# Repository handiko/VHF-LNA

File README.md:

# MMIC VHF Low Noise Amplifier
VHF Low Noise Amplifier Circuit &amp; PCB using common MMIC. This unit is capable up to 1kW at 2m-band (144 MHz) and powered by +12V supply thru a separate cable (hi-power bias tee is not implemented). MMIC input is protected by a BPF. Therefore, due to the BPF insertion loss, the input NF is not extremely good, (only 1 dB NF approx.). All the Eagle and Gerber files are included.

## Schematic

## PCB (photos)
* Unpopulated

* Populated. The input port is at near the lower right relay and the output port is at near the lower left relay.

## BPF Response
BPF simulation file (using RFSim99) is included also.
Predicted performance:
* **S21 -3dB from 135.67MHz - 150.07MHz**
* **S21 -10dB from 131.1MHz - 154.5MHz**
* **S21 -0.02dB and S11 -23.86dB at 139.1MHz** (WXSat band)
* **S21 -0.31dB and S11 -11.59dB at 143.02MHz** (BPF Center Frequency)
* **S21 -0.21dB and S11 -13.17dB at 144.3MHz** (EME Band)
* **S21 -0.04dB and S11 -20.69dB at 145.8MHz** (2m AMSAT Band)
* **FM Broadcast band rejection is better than -28dB (S21) at 108MHz**

## Contributing
1. Fork it [https://github.com/handiko/VHF-LNA/fork](https://github.com/handiko/VHF-LNA/fork)
2. Create new branch (`git checkout -b add-blah-blah`)
3. Do some editing / create new feature
4. Commit your works (`git commit -m "Adding some blah blah blah.."`)
5. Push to the branch (`git push -u origin add-blah-blah`)
6. Create a new Pull Request

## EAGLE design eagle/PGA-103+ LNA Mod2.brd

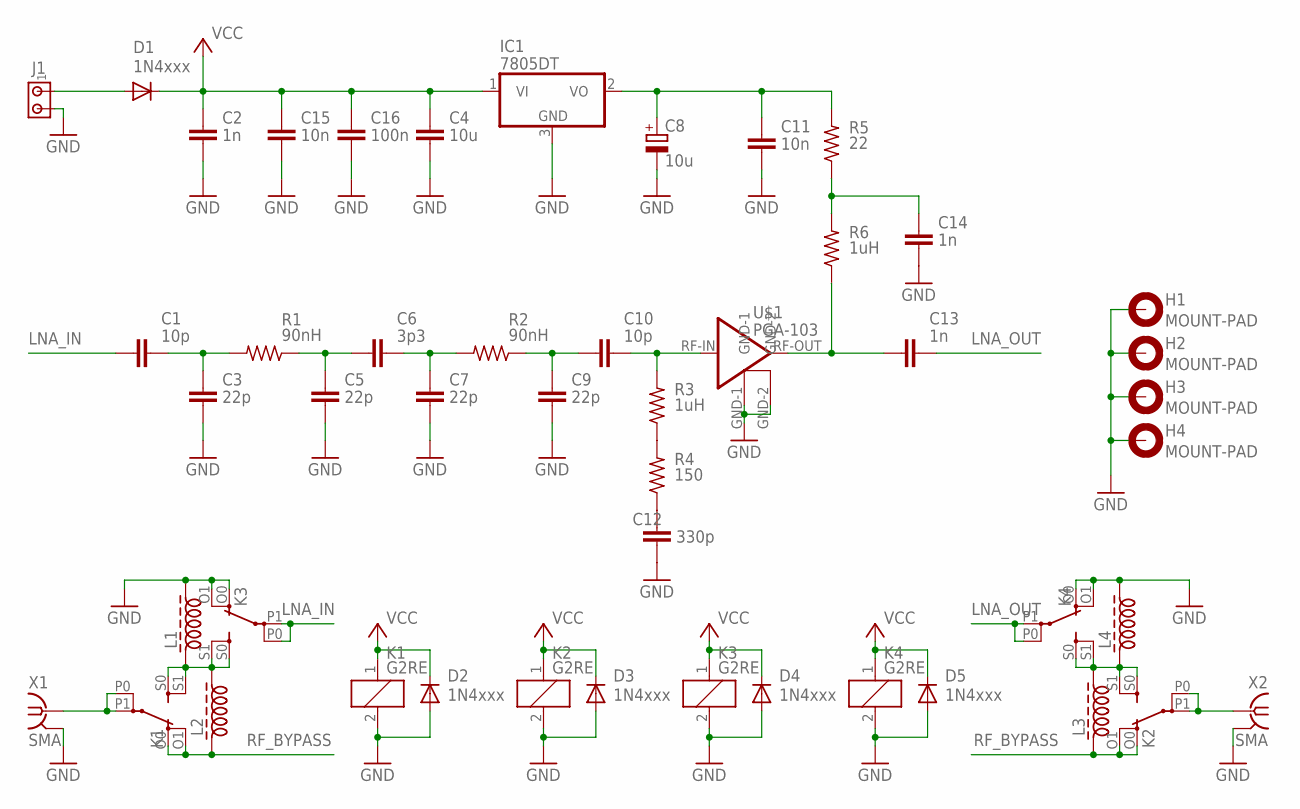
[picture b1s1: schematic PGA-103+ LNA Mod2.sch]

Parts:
C1, C10: 10p; C1206
C2, C13, C14: 1n; C1206
C3, C5, C7, C9: 22p; C1206
C4: 10u; C1206
C6: 3p3; C1206
C8: 10u; B/3528-21R
C11, C15: 10n; C1206
C12: 330p; C1206
C16: 100n; C1206
D1, D2, D3, D4, D5: 1N4xxx; DO35-7
H1, H2, H3, H4: MOUNT-PAD; 2,8-PAD
IC1: 7805DT; TO252
J1: MTA02-156; 1X2MTA
K1, K2, K3, K4: G2RE
L1, L2, L3, L4: Z28/70CW; Z28/7
R1, R2: 90nH; M1206
R3, R6: 1uH; M1206
R4: 150; M1206
R5: 22; M1206
U$1: PGA-103; DF782
X1, X2: SMA; J502-ND-142-0701-851/861

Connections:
ANT: K1.P0, K1.P1, X1.1
GND: C2.2, C3.1, C4.2, C5.1, C7.1, C8.-, C9.1, C11.2, C12.1, C14.1, C15.2, C16.2, D2.A, D3.A, D4.A, D5.A, H1.B2,8, H2.B2,8, H3.B2,8, H4.B2,8, IC1.3 (GND), J1.2, K1.2, K2.2, K3.2, K3.O0 (O), K3.O1 (O), K4.2, K4.O0 (O), K4.O1 (O), L1.2, L4.2, U$1.GND-1, U$1.GND-2, X1.G@1 (2), X1.G@2 (2), X1.G@3 (2), X1.G@4 (2), X2.G@1 (2), X2.G@2 (2), X2.G@3 (2), X2.G@4 (2)
LNA_IN: C1.1, K3.P0, K3.P1
LNA_OUT: C13.2, K4.P0, K4.P1
unnamed: C10.2, R3.2, U$1.RF-IN
unnamed: C13.1, R6.1, U$1.RF-OUT
unnamed: C8.+, C11.1, IC1.2 (VO), R5.2
unnamed: D1.A, J1.1
unnamed: C9.2, C10.1, R2.1
unnamed: C14.2, R5.1, R6.2
unnamed: R3.1, R4.2
unnamed: C12.2, R4.1
unnamed: C6.2, C7.2, R2.2
unnamed: C5.2, C6.1, R1.1
unnamed: C1.2, C3.2, R1.2
unnamed: K1.S0 (S), K1.S1 (S), K3.S0 (S), K3.S1 (S), L1.1, L2.2
unnamed: K2.S0 (S), K2.S1 (S), K4.S0 (S), K4.S1 (S), L3.2, L4.1
RF_BYPASS: K1.O0 (O), K1.O1 (O), K2.O0 (O), K2.O1 (O), L2.1, L3.1
TRX: K2.P0, K2.P1, X2.1
VCC: C2.1, C4.1, C15.1, C16.1, D1.C, D2.C, D3.C, D4.C, D5.C, IC1.1 (VI), K1.1, K2.1, K3.1, K4.1

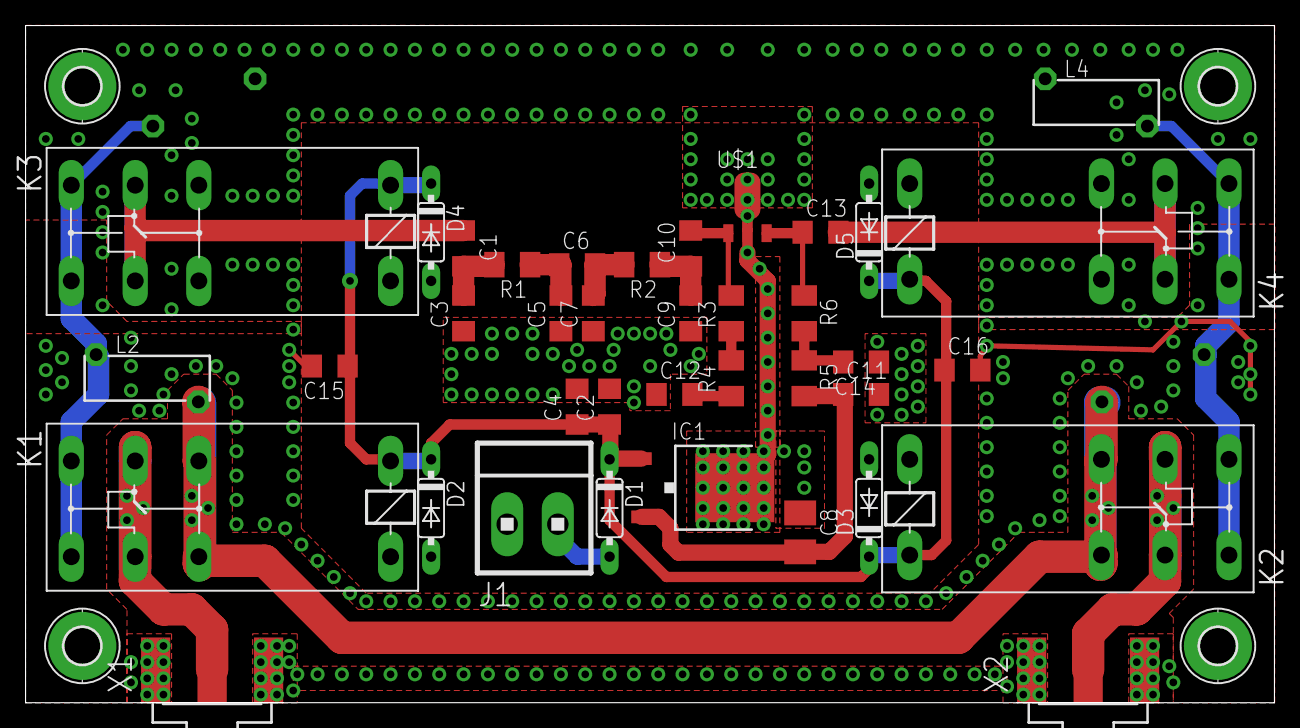
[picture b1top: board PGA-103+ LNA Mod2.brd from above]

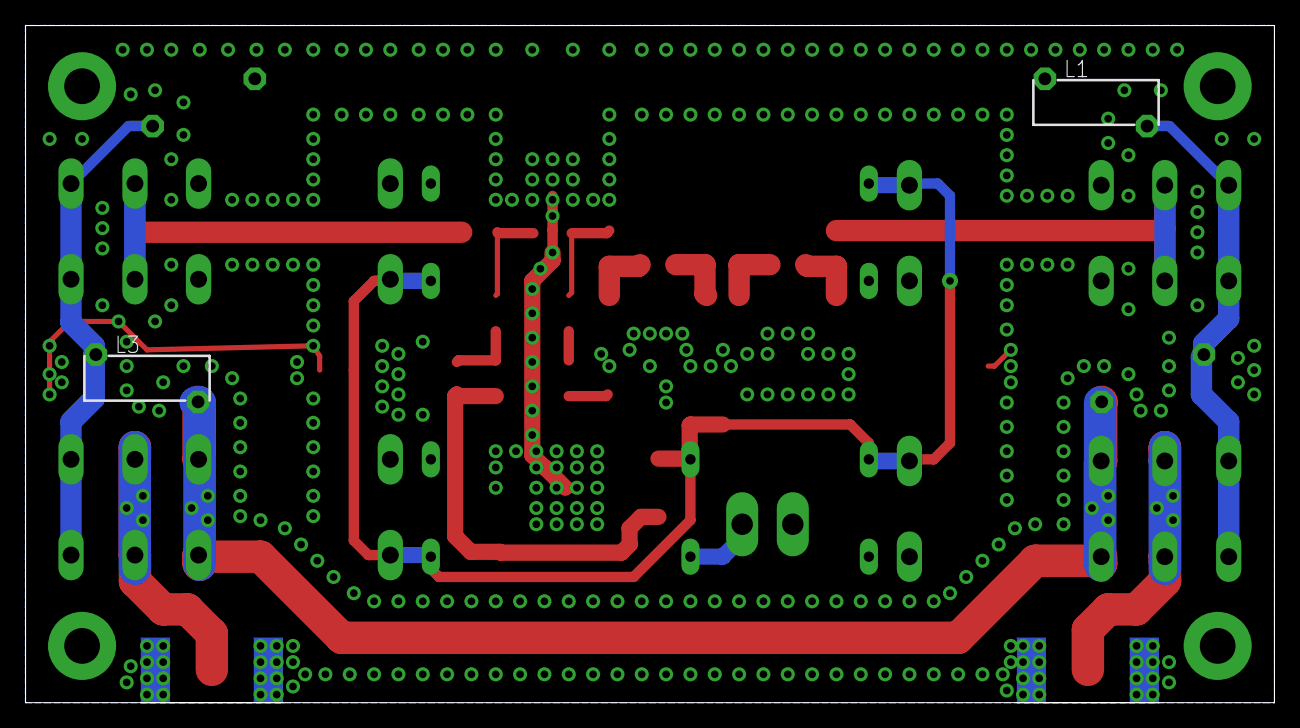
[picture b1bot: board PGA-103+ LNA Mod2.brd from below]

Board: 2 copper layers, 97.8 x 53.0 mm, 44 parts (2 on the bottom side), 20 nets.

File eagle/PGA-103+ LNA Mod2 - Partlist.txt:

Partlist

Exported from PGA-103+ LNA Mod2.sch at 11/7/2018 9:07 PM

EAGLE Version 7.7.0 Copyright (c) 1988-2016 CadSoft

Assembly variant: 

Part     Value          Device               Package                  Library         Sheet

C1       10p            C-EUC1206            C1206                    rcl             1
C2       1n             C-EUC1206            C1206                    rcl             1
C3       22p            C-EUC1206            C1206                    rcl             1
C4       10u            C-EUC1206            C1206                    rcl             1
C5       22p            C-EUC1206            C1206                    rcl             1
C6       3p3            C-EUC1206            C1206                    rcl             1
C7       22p            C-EUC1206            C1206                    rcl             1
C8       10u            CPOL-EUB/3528-21R    B/3528-21R               rcl             1
C9       22p            C-EUC1206            C1206                    rcl             1
C10      10p            C-EUC1206            C1206                    rcl             1
C11      10n            C-EUC1206            C1206                    rcl             1
C12      330p           C-EUC1206            C1206                    rcl             1
C13      1n             C-EUC1206            C1206                    rcl             1
C14      1n             C-EUC1206            C1206                    rcl             1
C15      10n            C-EUC1206            C1206                    rcl             1
C16      100n           C-EUC1206            C1206                    rcl             1
D1       1N4xxx         1N4148DO35-7         DO35-7                   diode           1
D2       1N4xxx         1N4148DO35-7         DO35-7                   diode           1
D3       1N4xxx         1N4148DO35-7         DO35-7                   diode           1
D4       1N4xxx         1N4148DO35-7         DO35-7                   diode           1
D5       1N4xxx         1N4148DO35-7         DO35-7                   diode           1
H1       MOUNT-PAD      MOUNT-PAD-ROUND2.8   2,8-PAD                  holes           1
H2       MOUNT-PAD      MOUNT-PAD-ROUND2.8   2,8-PAD                  holes           1
H3       MOUNT-PAD      MOUNT-PAD-ROUND2.8   2,8-PAD                  holes           1
H4       MOUNT-PAD      MOUNT-PAD-ROUND2.8   2,8-PAD                  holes           1
IC1      7805DT         7805DT               TO252                    linear          1
J1                      MTA02-156            1X2MTA                   con-amp         1
K1       G2RE           G2RE                 G2RE                     relay           1
K2       G2RE           G2RE                 G2RE                     relay           1
K3       G2RE           G2RE                 G2RE                     relay           1
K4       G2RE           G2RE                 G2RE                     relay           1
L1                      Z28/70CW             Z28/7                    inductor-neosid 1
L2                      Z28/70CW             Z28/7                    inductor-neosid 1
L3                      Z28/70CW             Z28/7                    inductor-neosid 1
L4                      Z28/70CW             Z28/7                    inductor-neosid 1
R1       90nH           R-US_M1206           M1206                    rcl             1
R2       90nH           R-US_M1206           M1206                    rcl             1
R3       1uH            R-US_M1206           M1206                    rcl             1
R4       150            R-US_M1206           M1206                    rcl             1
R5       22             R-US_M1206           M1206                    rcl             1
R6       1uH            R-US_M1206           M1206                    rcl             1
U$1      PGA-103        PGA-103              DF782                    minicircuits    1
X1       SMA            SMA-142-0701-851/861 J502-ND-142-0701-851/861 con-coax        1
X2       SMA            SMA-142-0701-851/861 J502-ND-142-0701-851/861 con-coax        1

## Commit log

2018-12-29 Create LICENSE
2018-12-29 Adding Pics
2018-12-29 Adding RFSim99
2018-12-29 Adding Pic
2019-01-04 Adding gitignore
2019-01-04 Generate Gerber files
2019-01-09 Recompile
2019-01-10 Adding PDFs
2019-01-14 Set theme jekyll-theme-cayman
2019-01-14 restructuring readme.md
2020-04-28 Set theme jekyll-theme-dinky
